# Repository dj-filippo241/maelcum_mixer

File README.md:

# Maelcum Mixer

A one-off, fully analogue, modular dub performance mixer for a 5-way sound system.

Musical decisions and panel layout: Filippo. Engineering (topologies, simulations, PCB generation): Claude, under Filippo's review.

**Status.** Nothing has been built or measured on a bench yet. Every circuit number comes from LTspice simulation or from Python models. The musical behaviour (control laws, saturators, filter character) is being validated by ear on a Max for Live prototype. Component purchases are on hold until that prototype is complete. The PCBs are generated drafts.

## Start here

- **Technical dossier (English):** [`docs/dossier-en/maelcum-mixer-dossier.pdf`](docs/dossier-en/maelcum-mixer-dossier.pdf), also as [HTML](docs/dossier-en/dossier.html). It is the complete English entry point: architecture, every module, numbers and their sources.
- **Block diagrams (English):** [`docs/diagrammi/en/`](docs/diagrammi/en/index.html), starting from [`schema-totale.svg`](docs/diagrammi/en/schema-totale.svg).

The rest of the repository is written in Italian. Technical terms stay in English where they are standard (headroom, summing, feedback, taper).

## Architecture in one paragraph

Four DJ channels (CDJ/line, optional MM phono) with a 4-band isolator EQ and a VCA fader. A shared global filter (HPF and LPF buses after the fader, Xone:96-style law, OTA core with overdrive). A 5-way performance EQ / dub preamp with a kill per band, matching the crossover of the sound system. Four FX buses with a 16-VCA feedback matrix. Mic and generic mono modules. Master, booth and record outputs, CUE, metering in six zones. Design targets: 0 dBu nominal, system headroom of at least +24 dBu (master clips at about +25.5 dBu), no automatic dynamics, nonlinearity only where intended. Simulated system noise: about -83 dBu A-weighted with filters off.

## Repository map

| Path | Content |
|---|---|
| `SPECIFICA.md` | Consolidated specification |
| `docs/01-decisioni-bloccate.md` | Locked decisions, with date and origin |
| `docs/02-questioni-aperte.md` | Open questions |
| `docs/fase1/` ... `docs/fase4/` | Design documents per module |
| `sim/` | LTspice netlists (`.cir`) and results (`RISULTATI-*.md`); shared models in `sim/lib/` |
| `pcb/` | KiCad schematics and 4-layer PCBs, generated by `pcb/<module>/<module>.py` with `pcb/tools/pcbgen.py` |
| `proto-max/` | Max for Live prototype: generators and tests in `proto-max/coefficienti/` |
| `docs/pannelli/` | Panel renders |
| `cheap/` | A parallel low-cost variant, on hold |

Status tags used in the documents: BLOCCATO (locked), PROVVISORIO (provisional), APERTO (open), SUPERATO (superseded, kept as an alternative or as evidence of a dead end).

## Tools

- LTspice 26.0.2, run in batch with `sim/run_ltspice.sh <netlist.cir>`.
- KiCad 10.0.7 with Freerouting; boards are regenerated from their Python script, never edited by hand.
- Max for Live (gen~) for the prototype; the `.genexpr`, `.maxpat` and `.amxd` files are generated.

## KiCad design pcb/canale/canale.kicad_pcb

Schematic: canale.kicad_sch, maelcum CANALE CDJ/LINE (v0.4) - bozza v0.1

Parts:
C1, C2: 220u 35V; CP_Radial_D8.0mm_P3.50mm
C3: 47u 10V; CP_Radial_D5.0mm_P2.00mm
C4, C8: 10u 35V; CP_Radial_D5.0mm_P2.00mm
C5, C9: 47u 35V; CP_Radial_D6.3mm_P2.50mm
C6, C10: 470u 25V; CP_Radial_D8.0mm_P3.50mm
C7, C11: 100u 25V; CP_Radial_D6.3mm_P2.50mm
C12, C13: 1u 50V; C_1206_3216Metric
C14, C15: 1u 25V; C_1206_3216Metric
C16, C17, C19, C20: 4u7 25V; C_1206_3216Metric
C18, C21: 10u 25V; C_1206_3216Metric
C22: 1u; C_1206_3216Metric
C23, C24, C27, C28, C29, C30, C58, C59, C60, C61, C62, C63, C64, C65, C66, C67, C96, C97, C98, C99, C100, C101, C102, C103, C104, C105, C107, C108, C109, C110, C111, C112, C113, C114, C117, C118, C119, C120, C122, C123, C125, C126, C127, C128, C131, C132, C133, C134, C135, C136, C137, C139, C140, C141, C142, C143: 100n; C_0805_2012Metric
C25, C26: 2u2 film; C_1812_4532Metric
C31, C32, C42, C43, C69, C70, C80, C81: 220n C0G; C_1210_3225Metric
C33, C34, C35, C36, C49, C51, C71, C72, C73, C74, C87, C89: 100n C0G; C_1210_3225Metric
C37, C38, C39, C40, C41, C57, C75, C76, C77, C78, C79, C95: 10n C0G; C_1206_3216Metric
C44, C82: 94n C0G; C_1210_3225Metric
C45, C83: 47n C0G; C_1210_3225Metric
C46, C52, C84, C90: 9n4 C0G; C_1206_3216Metric
C47, C53, C55, C85, C91, C93: 4n7 C0G; C_1206_3216Metric
C48, C50, C86, C88: 200n C0G; C_1210_3225Metric
C54, C92: 21n15 C0G; C_1206_3216Metric
C56, C94: 20n C0G; C_1206_3216Metric
C68, C106: 27n C0G; C_1206_3216Metric
C115: 47p C0G; C_0805_2012Metric
C116: 100n C0G; C_1206_3216Metric
C121, C124: 22p C0G; C_0805_2012Metric
C129, C130: 50n C0G; C_1206_3216Metric
C138: 47n; C_0805_2012Metric
D1, D3, D8, D9, D10, D11, D12, D13, D14: 1N4148W; D_SOD-123
D2, D4: S1G; D_SMA
D5: LM4040-5.0; SOT-23
D6, D7: TVS bidir <=5 pF; D_SOD-323
FB1, FB2, FB3, FB4, FB5, FB6, FB7: ferrite 600R; L_1206_3216Metric
H1, H2, H3: CHASSIS; MountingHole_3.2mm_M3_Pad
J1: C96 maschio; DIN41612_C_3x32_Male_Horizontal_THT
J2: 2x18 cavo piatto; PinHeader_2x18_P2.54mm_Vertical
J3: 1x5 ingressi; PinHeader_1x05_P2.54mm_Vertical
Q40: BD139; TO-126-3_Vertical
Q41: BD140; TO-126-3_Vertical
R1, R4: 120 1%; R_0805_2012Metric
R2, R5: 1k74 1%; R_0805_2012Metric
R3, R6, R127, R164, R165: 1k; R_0805_2012Metric
R7, R8: 150k 0.1%; R_0805_2012Metric
R9: 1k5; R_0805_2012Metric
R10, R11, R37, R39, R43, R45, R53, R55, R86, R88, R92, R94, R102, R104, R146, R168, R169, R170, R171, R172, R173: 10k 0.1%; R_0805_2012Metric
R12, R17: 100; R_0805_2012Metric
R13, R18, R69, R118, R149, R162, R167: 100k; R_0805_2012Metric
R14, R19: 4k30 0.1%; R_0805_2012Metric
R15, R20: 2k15 0.1%; R_0805_2012Metric
R16, R21, R151, R153: 1k 0.1%; R_0805_2012Metric
R22, R23, R32, R33, R71, R72, R81, R82: 4k81 0.1%; R_0805_2012Metric
R24, R26, R46, R47, R48, R49, R73, R75, R95, R96, R97, R98: 3k20 0.1%; R_0805_2012Metric
R25, R27, R74, R76: 6k42 0.1%; R_0805_2012Metric
R28, R77: 2k37 0.1%; R_0805_2012Metric
R29, R78: 10k7 0.1%; R_0805_2012Metric
R30, R59, R60, R79, R108, R109: 3k57 0.1%; R_0805_2012Metric
R31, R80: 7k15 0.1%; R_0805_2012Metric
R34, R83: 6k81 0.1%; R_0805_2012Metric
R35, R84: 13k7 0.1%; R_0805_2012Metric
R36, R85: 10k2 0.1%; R_0805_2012Metric
R38, R44, R54, R87, R93, R103, R157: 4k99 0.1%; R_0805_2012Metric
R40, R50, R89, R99: 7k59 0.1%; R_0805_2012Metric
R41, R51, R90, R100: 15k2 0.1%; R_0805_2012Metric
R42, R52, R91, R101: 11k4 0.1%; R_0805_2012Metric
R56, R57, R58, R105, R106, R107: 5k05 0.1%; R_0805_2012Metric
R61, R62, R63, R64, R110, R111, R112, R113: 2k49 0.1%; R_0805_2012Metric
R65, R114: 2k 0.1%; R_0805_2012Metric
R66, R115: 1k8 0.1%; R_0805_2012Metric
R67, R116: 200 0.1%; R_0805_2012Metric
R68, R117: 1M; R_0805_2012Metric
R70, R119: 499 0.1%; R_0805_2012Metric
R120, R121, R122, R123: 47; R_0805_2012Metric
R124, R125, R129, R133, R134, R138: 20k 0.1%; R_0805_2012Metric
R126: 4k02 0.1%; R_0805_2012Metric
R128: 3M; R_0805_2012Metric
R130, R135: 6k19; R_0805_2012Metric
R131, R136: 150k; R_0805_2012Metric
R132, R137: 51; R_0805_2012Metric
R139: 43.2k 0.1%; R_0805_2012Metric
R140: 68.1k 0.1%; R_0805_2012Metric
R141: 357k 0.1%; R_0805_2012Metric
R142: 20.0k 0.1%; R_0805_2012Metric
R143: 38.3k 0.1%; R_0805_2012Metric
R144: 976 0.1%; R_0805_2012Metric
R145: 1.33k 0.1%; R_0805_2012Metric
R147: 9k76 0.1%; R_0805_2012Metric
R148: 18k7 0.1%; R_0805_2012Metric
R150: 18k2 0.1%; R_0805_2012Metric
R152: 17k4 0.1%; R_0805_2012Metric
R154: 2M7; R_0805_2012Metric
R155, R156, R158, R159, R160, R161, R166: 10k; R_0805_2012Metric
R163: 68k; R_0805_2012Metric
RV1, RV2, RV4: 50k; Potentiometer_Bourns_3266W_Vertical
RV3: 2k; Potentiometer_Bourns_3266W_Vertical
U1, U2, U13, U15, U16, U20, U21, U22, U46: OPA1612AIDR; SOIC-8_3.9x4.9mm_P1.27mm
U3, U4, U5, U6, U7, U8, U9, U10, U11, U12, U17: OPA1654AIDR; SOIC-14_3.9x8.7mm_P1.27mm
U14: OPA1642AIDR; SOIC-8_3.9x4.9mm_P1.27mm
U18, U19: V2181L; SOIC-8_3.9x4.9mm_P1.27mm
U23: 74HC14PW; TSSOP-14_4.4x5mm_P0.65mm
U24: 74HC86PW; TSSOP-14_4.4x5mm_P0.65mm
U25: 74HC74PW; TSSOP-14_4.4x5mm_P0.65mm
U26, U27: ADG1434YRUZ; TSSOP-20_4.4x6.5mm_P0.65mm
U40: LM317; TO-220-3_Vertical
U41: LM337; TO-220-3_Vertical
U42: 78L15; SOT-89-3
U43: 79L15; SOT-89-3
U44: LT3045EMSE; MSOP-12-1EP_3x4.039mm_P0.65mm_EP1.651x2.845mm
U45: LT3094EMSE; MSOP-12-1EP_3x4.039mm_P0.65mm_EP1.651x2.845mm

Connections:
+5V: FB5.1, J1.a21, J1.a22
+5VF: C3.1, C135.1, C136.1, C137.1, FB5.2, J2.33, R158.1, R160.1, U23.14 (VCC), U24.13 (4B), U24.14 (VCC), U25.1 (1CLR), U25.4 (1PRE), U25.10 (2PRE), U25.13 (2CLR), U25.14 (VCC)
+15LN: C18.1, C23.1, C127.1, C131.1, R9.1, RV1.1, RV2.1, RV4.1, U21.8 (V+), U22.8 (V+), U44.10 (OUTS), U44.11 (OUT), U44.12 (OUT), U46.8 (V+)
+15SW: C14.1, C140.1, C142.1, U26.16 (VDD), U27.16 (VDD), U42.1 (OUT)
+18V: C7.1, C17.1, C27.1, C29.1, C58.1, C60.1, C62.1, C64.1, C66.1, C96.1, C98.1, C100.1, C102.1, C104.1, C107.1, C109.1, C111.1, C113.1, C117.1, C119.1, C122.1, C125.1, Q40.1 (E), U1.8 (V+), U2.8 (V+), U3.4 (V+), U4.4 (V+), U5.4 (V+), U6.4 (V+), U7.4 (V+), U8.4 (V+), U9.4 (V+), U10.4 (V+), U11.4 (V+), U12.4 (V+), U13.8 (V+), U14.8 (V+), U15.8 (V+), U16.8 (V+), U17.4 (V+), U18.7 (V+), U19.7 (V+), U20.8 (V+), U44.1 (IN), U44.2 (IN), U44.3 (IN), U44.4 (EN/UV), U44.7 (PGFB)
+REF5: J2.26, R10.1, U46.1, U46.2 (-)
-15LN: C21.2, C24.2, C128.2, C132.2, RV1.3, RV2.3, RV4.3, U21.4 (V-), U22.4 (V-), U45.10 (OUTS), U45.11 (OUT), U45.12 (OUT), U46.4 (V-)
-15SW: C15.2, C141.2, C143.2, U26.5 (VSS), U27.5 (VSS), U43.3 (VO)
-18V: C11.2, C20.2, C28.2, C30.2, C59.2, C61.2, C63.2, C65.2, C67.2, C97.2, C99.2, C101.2, C103.2, C105.2, C108.2, C110.2, C112.2, C114.2, C118.2, C120.2, C123.2, C126.2, Q41.1 (E), R130.2, R135.2, U1.4 (V-), U2.4 (V-), U3.11 (V-), U4.11 (V-), U5.11 (V-), U6.11 (V-), U7.11 (V-), U8.11 (V-), U9.11 (V-), U10.11 (V-), U11.11 (V-), U12.11 (V-), U13.4 (V-), U14.4 (V-), U15.4 (V-), U16.4 (V-), U17.11 (V-), U20.4 (V-), U45.1 (IN), U45.2 (IN), U45.3 (EN/UV), U45.5 (PGFB), U45.13 (IN)
-REF5: R11.2, R141.2, R143.2, R145.2, U46.7
ADJ+: C4.1, D1.2 (A), R1.2, R2.1, U40.1 (ADJ)
ADJ-: C8.2, D3.1 (K), R4.2, R5.1, U41.1 (ADJ)
AGND: C1.2, C2.1, C4.2, C5.2, C6.2, C7.2, C8.1, C9.1, C10.1, C11.1, C12.2, C13.1, C14.2, C15.1, C16.2, C17.2, C18.2, C19.1, C20.1, C21.1, C22.2, C23.2, C24.1, C27.2, C28.1, C29.2, C30.1, C43.2, C49.2, C51.2, C54.2, C57.2, C58.2, C59.1, C60.2, C61.1, C62.2, C63.1, C64.2, C65.1, C66.2, C67.1, C81.2, C87.2, C89.2, C92.2, C95.2, C96.2, C97.1, C98.2, C99.1, C100.2, C101.1, C102.2, C103.1, C104.2, C105.1, C107.2, C108.1, C109.2, C110.1, C111.2, C112.1, C113.2, C114.1, C116.2, C117.2, C118.1, C119.2, C120.1, C122.2, C123.1, C125.2, C126.1, C127.2, C128.1, C129.2, C130.2, C131.2, C132.1, C140.2, C141.1, C142.2, C143.1, D5.2 (A), D6.2 (A2), D7.2 (A2), J1.a13, J1.a14, J1.a15, J1.a16, J1.a17, J1.a18, J1.a19, J1.a20, J1.b3, J1.b6, J1.b9, J1.b12, J1.b15, J1.b18, J1.b21, J1.b24, J1.b27, J1.b30, J2.1, J2.4, J2.7, J2.16, J2.25, J2.28, J2.35, J2.36, J3.2, J3.4, R2.2, R5.2, R7.2, R8.2, R13.2, R14.2, R16.2, R18.2, R19.2, R21.2, R23.2, R25.2, R27.2, R28.2, R31.2, R35.2, R41.2, R51.2, R67.2, R70.2, R72.2, R74.2, R76.2, R77.2, R80.2, R84.2, R90.2, R100.2, R116.2, R119.2, R126.2, R128.2, R132.2, R137.2, R149.2, R151.2, R153.2, U3.12 (+), U4.10 (+), U4.12 (+), U5.3 (+), U5.5 (+), U6.3 (+), U6.5 (+), U6.10 (+), U8.12 (+), U9.10 (+), U9.12 (+), U10.3 (+), U10.5 (+), U11.3 (+), U11.5 (+), U11.10 (+), U14.3 (+), U14.5 (+), U17.12 (+), U18.2 (EC+), U18.6 (GND), U19.2 (EC+), U19.6 (GND), U20.3 (+), U20.5 (+), U21.3 (+), U21.5 (+), U26.4 (S1B), U26.6 (GND), U26.7 (S2B), U26.14 (S3B), U26.17 (S4B), U27.4 (S1B), U27.6 (GND), U27.7 (S2B), U27.14 (S3B), U27.17 (S4B), U42.2 (GND), U43.1 (GND), U44.6 (ILIM), U44.9 (GND), U44.13 (GND), U45.6 (ILIM), U45.9 (GND), U46.5 (+)
APBP1_L: C45.2, R36.2, R38.1, U4.8
APBP1_R: C83.2, R85.2, R87.1, U9.8
APBP2_L: C47.2, R42.2, R44.1, U5.1
APBP2_R: C85.2, R91.2, R93.1, U10.1
APBP3_L: C53.2, R52.2, R54.1, U6.1
APBP3_R: C91.2, R101.2, R103.1, U11.1
APMP1_L: C44.2, R36.1, U4.9 (-)
APMP1_R: C82.2, R85.1, U9.9 (-)
APMP2_L: C46.2, R42.1, U5.2 (-)
APMP2_R: C84.2, R91.1, U10.2 (-)
APMP3_L: C52.2, R52.1, U6.2 (-)
APMP3_R: C90.2, R101.1, U11.2 (-)
APNP1_L: C44.1, C45.1, R34.2, R35.1
APNP1_R: C82.1, C83.1, R83.2, R84.1
APNP2_L: C46.1, C47.1, R40.2, R41.1
APNP2_R: C84.1, C85.1, R89.2, R90.1
APNP3_L: C52.1, C53.1, R50.2, R51.1
APNP3_R: C90.1, C91.1, R99.2, R100.1
APSP1_L: R37.2, R38.2, R39.1, U4.13 (-)
APSP1_R: R86.2, R87.2, R88.1, U9.13 (-)
APSP2_L: R43.2, R44.2, R45.1, U5.6 (-)
APSP2_R: R92.2, R93.2, R94.1, U10.6 (-)
APSP3_L: R53.2, R54.2, R55.1, U6.6 (-)
APSP3_R: R102.2, R103.2, R104.1, U11.6 (-)
BASE+: C6.1, Q40.3 (B), R3.2
BASE-: C10.2, Q41.3 (B), R6.2
BTNC: J2.32, R166.1
BUF_L: J2.2, U1.1, U1.2 (-)
BUF_R: J2.5, U1.6 (-), U1.7
BUS_HPF_L: J1.b10, R169.2
BUS_HPF_R: J1.b11, R172.2
BUS_LPF_L: J1.b13, R170.2
BUS_LPF_R: J1.b14, R173.2
CHASSIS: H1.1, H2.1, H3.1, J1.a25, J1.a26, J3.5
CLK: U23.8 (4Y), U25.3 (1CLK), U25.11 (2CLK)
CTRL_GND: C3.2, C133.2, C134.2, C135.2, C136.2, C137.2, C138.2, C139.2, J1.a23, J1.a24, J1.c16, J1.c20, J1.c24, J1.c28, J2.34, R162.2, R167.2, U23.7 (GND), U24.7 (GND), U25.7 (GND)
CUEB_L: U15.1, U15.2 (-), U26.19 (S4A)
CUEB_R: U16.1, U16.2 (-), U27.19 (S4A)
CUED_L: R121.1, U26.18 (D4)
CUED_R: R123.1, U27.18 (D4)
CUESEL: C139.1, R166.2, R167.1, U26.20 (IN4), U27.20 (IN4)
CUE_OUT_L: J1.b4, R121.2
CUE_OUT_R: J1.b5, R123.2
CVP_F: R148.2, R150.1, R152.1, U21.7
D0: U23.2 (1Y), U24.1 (1A), U25.2 (1D)
D1: U23.4 (2Y), U24.4 (2A), U25.12 (2D)
D1A: D8.2 (A), R127.2
DIFF: D12.1 (K), D13.1 (K), R162.1, U23.13 (6A)
DIFFB: D14.1 (K), R155.1, R163.1, U24.11 (4Y)
DIPCV: R157.1, U22.6 (-), U22.7
DJBUS_L: J1.b1, R168.2
DJBUS_R: J1.b2, R171.2
DJD_L: R168.1, U26.3 (D1)
DJD_R: R171.1, U27.3 (D1)
DJSEL: U23.10 (5Y), U26.1 (IN1), U27.1 (IN1)
DLY: C138.1, D14.2 (A), R163.2, U23.5 (3A)
DOUT: C115.1, R127.1, U17.7
DP1: C129.1, R155.2, U22.3 (+)
DP2: C130.1, R156.2, U22.5 (+)
DPB1: R156.1, U22.1, U22.2 (-)
ECF_L: R150.2, R151.1, U18.3 (EC-)
ECF_R: R153.1, R154.2, RV3.2, RV3.3, U19.3 (EC-)
EQ_L: R66.2, R68.1, R124.1, R129.1, U13.1, U15.3 (+), U15.5 (+)
EQ_R: R115.2, R117.1, R125.1, R134.1, U13.7, U16.3 (+), U16.5 (+)
FAD_L: C121.2, R133.2, U20.1, U26.2 (S1A), U26.9 (S2A), U26.12 (S3A)
FAD_R: C124.2, R138.2, U20.7, U27.2 (S1A), U27.9 (S2A), U27.12 (S3A)
FILT_MODE1_0: J1.c1, R164.2
FILT_MODE1_1: J1.c2, R165.2
FR0: C133.1, R159.2, U23.1 (1A)
FR1: C134.1, R161.2, U23.3 (2A)
FSW0: J2.30, R158.2, R159.1
FSW1: J2.31, R160.2, R161.1
GO_L: C31.1, R15.1, R32.1, U2.1
GO_R: C69.1, R20.1, R81.1, U2.7
GW_L: J2.3, R14.1, U2.3 (+)
GW_R: J2.6, R19.1, U2.5 (+)
HA_L: C55.2, R57.2, R59.1, U6.8
HA_R: C93.2, R106.2, R108.1, U11.8
HIO_L: J2.14, R30.2, U4.1, U4.2 (-)
HIO_R: J2.23, R79.2, U9.1, U9.2 (-)
HOLD: C115.2, C116.1, D8.1 (K), R128.1, U17.6 (-), U17.10 (+)
HPD_L: R169.1, U26.8 (D2)
HPD_R: R172.1, U27.8 (D2)
INC_L: C25.2, R13.1, U1.3 (+)
INC_R: C26.2, R18.1, U1.5 (+)
INF_L: FB6.2, R12.1
INF_R: FB7.2, R17.1
INP_L: C25.1, D6.1 (A1), R12.2
INP_R: C26.1, D7.1 (A1), R17.2
IN_L: FB6.1, J3.1
IN_R: FB7.1, J3.3
K1W_L: J2.9, U7.3 (+)
K1W_R: J2.18, U12.3 (+)
K1_L: R61.1, U7.1, U7.2 (-)
K1_R: R110.1, U12.1, U12.2 (-)
K2W_L: J2.11, U7.5 (+)
K2W_R: J2.20, U12.5 (+)
K2_L: R62.1, U7.6 (-), U7.7
K2_R: R111.1, U12.6 (-), U12.7
K3W_L: J2.13, U7.10 (+)
K3W_R: J2.22, U12.10 (+)
K3_L: R63.1, U7.8, U7.9 (-)
K3_R: R112.1, U12.8, U12.9 (-)
K4W_L: J2.15, U7.12 (+)
K4W_R: J2.24, U12.12 (+)
K4_L: R64.1, U7.13 (-), U7.14
K4_R: R113.1, U12.13 (-), U12.14
LA_L: C42.2, R34.1, R37.1, U4.6 (-), U4.7
LA_R: C80.2, R83.1, R86.1, U9.6 (-), U9.7
LB_L: R39.2, R40.1, R43.1, U4.14
LB_R: R88.2, R89.1, R92.1, U9.14
LMO_L: J2.10, R55.2, U6.7
LMO_R: J2.19, R104.2, U11.7
LOO_L: J2.8, R45.2, U5.7
LOO_R: J2.17, R94.2, U10.7
LPD_L: R170.1, U26.13 (D3)
LPD_R: R173.1, U27.13 (D3)
LT_F: R152.2, RV3.1
MA_L: C48.2, R48.1, U5.8, U5.9 (-)
MA_R: C86.2, R97.1, U10.8, U10.9 (-)
MB_L: C50.2, R50.1, R53.1, U5.13 (-), U5.14
MB_R: C88.2, R99.1, R102.1, U10.13 (-), U10.14
MCN_L: C55.1, R58.2, U6.9 (-)
MCN_R: C93.1, R107.2, U11.9 (-)
MCX_L: C54.1, R56.2, R57.1, R58.1
MCX_R: C92.1, R105.2, R106.1, R107.1
MET: J2.29, U17.8, U17.9 (-)
MG: R124.2, R125.2, R126.1, U17.3 (+)
MGB: U17.1, U17.2 (-), U17.5 (+)
MHN_L: C39.2, R29.1, U3.13 (-)
MHN_R: C77.2, R78.1, U8.13 (-)
MHO_L: C56.2, J2.12, U6.13 (-), U6.14
MHO_R: C94.2, J2.21, U11.13 (-), U11.14
MHX_L: C37.2, C38.1, C39.1, R28.1
MHX_R: C75.2, C76.1, C77.1, R77.1
NCLK: U23.6 (3Y), U23.9 (4A)
NDIFF: U23.12 (6Y), U24.12 (4A)
NGS_L: R66.1, R67.1, U13.2 (-)
NGS_R: R115.1, R116.1, U13.6 (-)
NG_L: R15.2, R16.1, U2.2 (-)
NG_R: R20.2, R21.1, U2.6 (-)
NIF_L: C121.1, R133.1, U18.8 (OUT), U20.2 (-)
NIF_R: C124.1, R138.1, U19.8 (OUT), U20.6 (-)
NP_F: R147.2, R148.1, U21.6 (-)
NREF5I: R10.2, R11.1, U46.6 (-)
NU17: U17.13 (-), U17.14
OF_F: R154.1, RV4.2
POT_F: J2.27, R139.1, R140.1, R142.1, R144.1, R149.1
Q0: R164.1, U24.2 (1B), U24.9 (3A), U25.5 (1Q), U26.10 (IN2), U27.10 (IN2)
Q1: R165.1, U24.5 (2B), U24.10 (3B), U25.9 (2Q), U26.11 (IN3), U27.11 (IN3)
R1_L: C33.1, R22.2, R46.1, U3.1, U3.2 (-)
R1_R: C71.1, R71.2, R95.1, U8.1, U8.2 (-)
R2A_L: C35.1, R24.2, U3.6 (-), U3.7
R2A_R: C73.1, R73.2, U8.6 (-), U8.7
R2_L: C37.1, R26.2, R56.1, U3.8, U3.9 (-)
R2_R: C75.1, R75.2, R105.1, U8.8, U8.9 (-)
R3A_L: C38.2, C40.1, R29.2, U3.14
R3A_R: C76.2, C78.1, R78.2, U8.14
RAW+22: FB3.1, J1.a5, J1.a6
RAW+27: FB1.1, J1.a1, J1.a2
RAW-22: FB4.1, J1.a7, J1.a8
RAW-27: FB2.1, J1.a3, J1.a4
REF5K: C22.1, D5.1 (K), R9.2, U46.3 (+)
SEND_TAP_L: J1.b7, R120.2
SEND_TAP_R: J1.b8, R122.2
SETN: C19.2, R8.1, U45.8 (SET)
SETP: C16.1, R7.1, U44.8 (SET)
SH_F: R146.2, R147.1, U21.1
SJ_F: D9.1 (K), D10.1 (K), D11.1 (K), R139.2, R146.1, R157.2, U21.2 (-)
SKAA1_L: C42.1, R32.2, R33.1
SKAA1_R: C80.1, R81.2, R82.1
SKAB1_L: C48.1, R46.2, R47.1
SKAB1_R: C86.1, R95.2, R96.1
SKAB2_L: C50.1, R48.2, R49.1
SKAB2_R: C88.1, R97.2, R98.1
SKAC2_L: C56.1, R59.2, R60.1
SKAC2_R: C94.1, R108.2, R109.1
SKAG2_L: C35.2, C36.1, R26.1
SKAG2_R: C73.2, C74.1, R75.1
SKAH1_L: C31.2, C32.1, R22.1
SKAH1_R: C69.2, C70.1, R71.1
SKAH2_L: C33.2, C34.1, R24.1
SKAH2_R: C71.2, C72.1, R73.1
SKAH3B_L: C40.2, C41.1, R30.1
SKAH3B_R: C78.2, C79.1, R79.1
SKBA1_L: C43.1, R33.2, U4.5 (+)
SKBA1_R: C81.1, R82.2, U9.5 (+)
SKBB1_L: C49.1, R47.2, U5.10 (+)
SKBB1_R: C87.1, R96.2, U10.10 (+)
SKBB2_L: C51.1, R49.2, U5.12 (+)
SKBB2_R: C89.1, R98.2, U10.12 (+)
SKBC2_L: C57.1, R60.2, U6.12 (+)
SKBC2_R: C95.1, R109.2, U11.12 (+)
SKBG2_L: C36.2, R27.1, U3.10 (+)
SKBG2_R: C74.2, R76.1, U8.10 (+)
SKBH1_L: C32.2, R23.1, U3.3 (+)
SKBH1_R: C70.2, R72.1, U8.3 (+)
SKBH2_L: C34.2, R25.1, U3.5 (+)
SKBH2_R: C72.2, R74.1, U8.5 (+)
SKBH3B_L: C41.2, R31.1, U4.3 (+)
SKBH3B_R: C79.2, R80.1, U9.3 (+)
SN1_F: D9.2 (A), R140.2, R141.1
SN2_F: D10.2 (A), R142.2, R143.1
SN3_F: D11.2 (A), R144.2, R145.1
SP_L: R61.2, R62.2, R63.2, R64.2, R65.2, U13.3 (+)
SP_R: R110.2, R111.2, R112.2, R113.2, R114.2, U13.5 (+)
STB_L: R120.1, U15.6 (-), U15.7
STB_R: R122.1, U16.6 (-), U16.7
SVI_L: C68.1, R68.2, U14.2 (-)
SVI_R: C106.1, R117.2, U14.6 (-)
SVO_L: C68.2, R69.1, U14.1
SVO_R: C106.2, R118.1, U14.7
SV_L: R65.1, R69.2, R70.1
SV_R: R114.1, R118.2, R119.1
SW_fl: R131.1, RV1.2
SW_fr: R136.1, RV2.2
SYM_fl: R131.2, R132.1, U18.4 (SYM)
SYM_fr: R136.2, R137.1, U19.4 (SYM)
V22F+: C12.1, FB3.2, U42.3 (IN)
V22F-: C13.2, FB4.2, U43.2 (VI)
V27F+: C1.1, D2.1 (K), FB1.2, U40.3 (VI)
V27F-: C2.2, D4.2 (A), FB2.2, U41.2 (VI)
VEE_fl: R130.1, U18.5 (V-)
VEE_fr: R135.1, U19.5 (V-)
VIN_fl: R129.2, U18.1 (IN)
VIN_fr: R134.2, U19.1 (IN)
VREG+: C5.1, D1.1 (K), D2.2 (A), Q40.2 (C), R1.1, R3.1, U40.2 (VO)
VREG-: C9.2, D3.2 (A), D4.1 (K), Q41.2 (C), R4.1, R6.1, U41.3 (VO)
X0: D12.2 (A), U24.3 (1Y)
X1: D13.2 (A), U24.6 (2Y)
XQ: U23.11 (5A), U24.8 (3Y)

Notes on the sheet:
BACKPLANE C96 (classe CDJ, REV dec. 159)
ALIMENTAZIONE +-18 audio, +-15 switch, +5, +-15 LN, +-5 riferimento
INGRESSO LINE [A] e GAIN T1 [B] (dec. 162)
ISOLATOR lato L (incroci C, dec. 152; iso-incc-banca.inc)
ISOLATOR lato R (incroci C, dec. 152; iso-incc-banca.inc)
SOMMA DELL'ISOLATOR (non invertente) e SERVO DC
CUE [D], SEND TAP [E] e METER [G] (pre-fader)
FADER [H] (2 VCA, shaper del fader, dec. 126) e DIP (dec. 163)
LEVETTA HPF/OFF/LPF: logica autotemporizzata (74HC14, 74HC86, 74HC74) e ADG1434
CAVO SCHEDA COMANDI (J2) e INGRESSI RCA (J3)

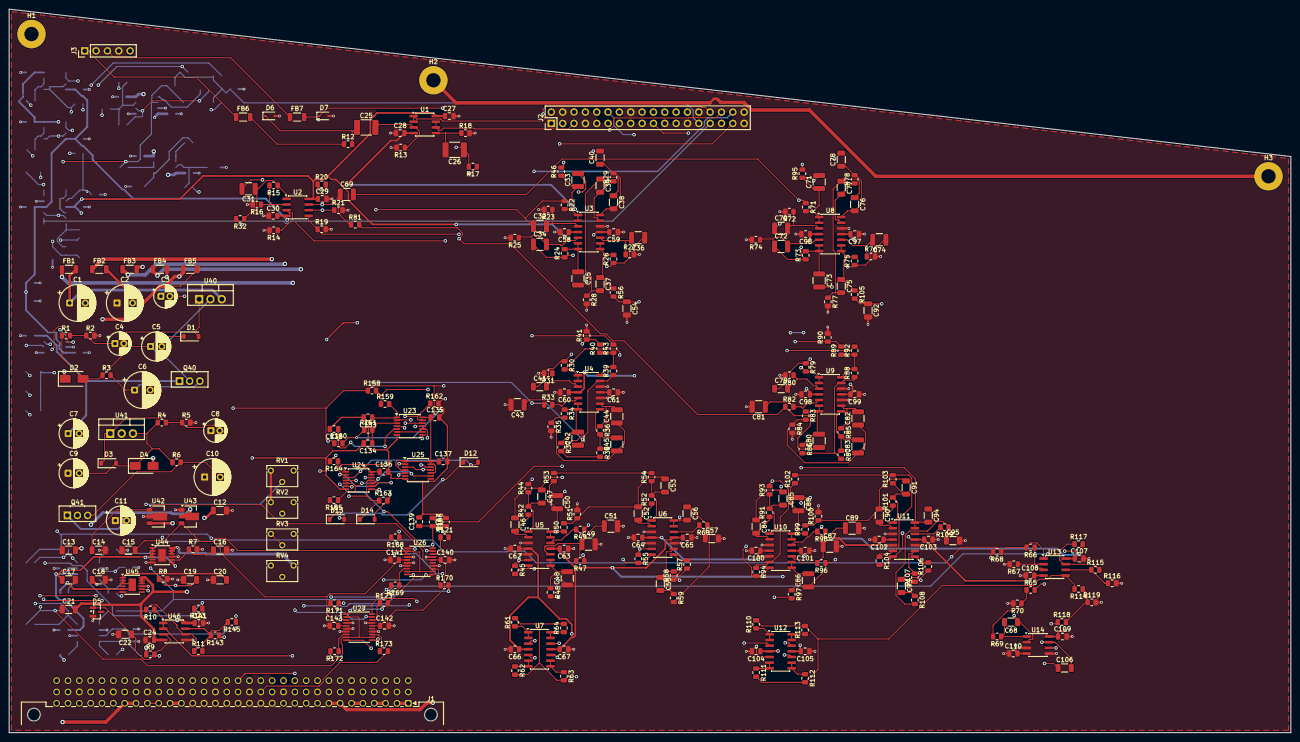
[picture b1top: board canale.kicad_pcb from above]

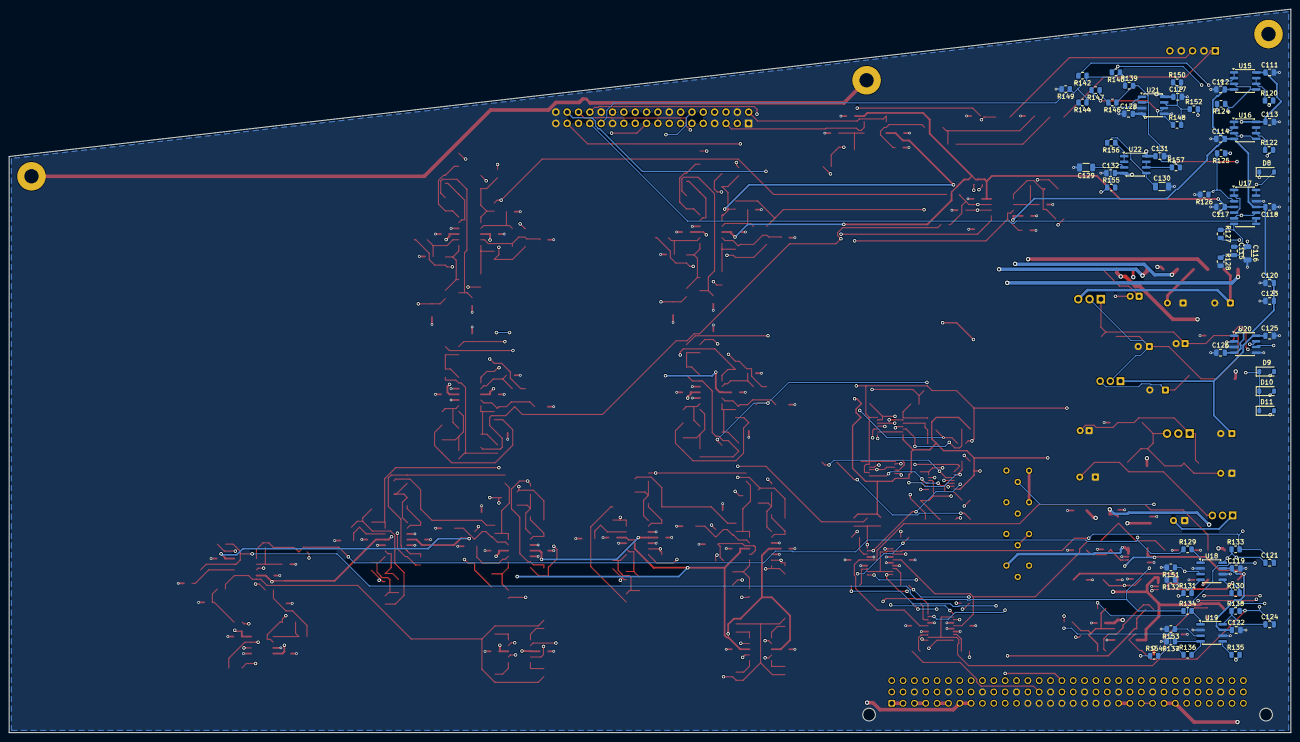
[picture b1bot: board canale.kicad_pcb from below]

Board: 4 copper layers, 287.0 x 162.0 mm, 383 parts (67 on the bottom side), 244 nets.

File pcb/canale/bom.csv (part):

quantita;valore;impronta;riferimenti;nota
2;220u 35V;CP_Radial_D8.0mm_P3.50mm;C1 C2;
1;47p C0G;C_0805_2012Metric;C115;
1;100n C0G;C_1206_3216Metric;C116;hold: niente altro sul nodo (sim/meter)
2;1u 50V;C_1206_3216Metric;C12 C13;
2;22p C0G;C_0805_2012Metric;C121 C124;
1;50n C0G;C_1206_3216Metric;C129;NOTA: 50n = 47n + 3n3 in parallelo; tau 0,5 ms
1;50n C0G;C_1206_3216Metric;C130;NOTA: 50n = 47n + 3n3 in parallelo
1;47n;C_0805_2012Metric;C138;
2;1u 25V;C_1206_3216Metric;C14 C15;
1;4u7 25V;C_1206_3216Metric;C16;rumore del riferimento (datasheet: 4,7 uF)
3;4u7 25V;C_1206_3216Metric;C17 C19 C20;
2;10u 25V;C_1206_3216Metric;C18 C21;
1;1u;C_1206_3216Metric;C22;
56;100n;C_0805_2012Metric;C23 C24 C27 C28 C29 C30 C58 C59 C60 C61 C62 C63 C64 C65 C66 C67 C96 C97 C98 C99 C100 C101 C102 C103 C104 C105 C107 C108 C109 C110 C111 C112 C113 C114 C117 C118 C119 C120 C122 C123 C125 C126 C127 C128 C131 C132 C133 C134 C135 C136 C137 C139 C140 C141 C142 C143;
2;2u2 film;C_1812_4532Metric;C25 C26;blocco della continua (voce 58)
1;47u 10V;CP_Radial_D5.0mm_P2.00mm;C3;
8;220n C0G;C_1210_3225Metric;C31 C32 C42 C43 C69 C70 C80 C81;
12;100n C0G;C_1210_3225Metric;C33 C34 C35 C36 C49 C51 C71 C72 C73 C74 C87 C89;
12;10n C0G;C_1206_3216Metric;C37 C38 C39 C40 C41 C57 C75 C76 C77 C78 C79 C95;
2;10u 35V;CP_Radial_D5.0mm_P2.00mm;C4 C8;
2;94n C0G;C_1210_3225Metric;C44 C82;NOTA: 2C, coppia in parallelo da fissare col layout (RISULTATI-incroci-C §1)
2;47n C0G;C_1210_3225Metric;C45 C83;
4;9n4 C0G;C_1206_3216Metric;C46 C52 C84 C90;NOTA: 2C, coppia in parallelo da fissare col layout (RISULTATI-incroci-C §1)
6;4n7 C0G;C_1206_3216Metric;C47 C53 C55 C85 C91 C93;
4;200n C0G;C_1210_3225Metric;C48 C50 C86 C88;NOTA: coppia in parallelo da fissare col layout
2;47u 35V;CP_Radial_D6.3mm_P2.50mm;C5 C9;
2;21n15 C0G;C_1206_3216Metric;C54 C92;NOTA: 4,5 x 4,7n, coppia in parallelo da fissare col layout
2;20n C0G;C_1206_3216Metric;C56 C94;NOTA: coppia in parallelo da fissare col layout
2;470u 25V;CP_Radial_D8.0mm_P3.50mm;C6 C10;
2;27n C0G;C_1206_3216Metric;C68 C106;integratore 1M/27n
2;100u 25V;CP_Radial_D6.3mm_P2.50mm;C7 C11;
1;1N4148W;D_SOD-123;D1;scarica Cadj
1;1N4148W;D_SOD-123;D12;NOTA: OR a diodi
1;1N4148W;D_SOD-123;D14;scarica il ritardo al rilascio: CLK giù in pochi us (todo 289)
1;S1G;D_SMA;D2;protezione inversa
6;1N4148W;D_SOD-123;D3 D8 D9 D10 D11 D13;
1;S1G;D_SMA;D4;
1;LM4040-5.0;SOT-23;D5;
2;TVS bidir <=5 pF;D_SOD-323;D6 D7;NOTA: parte da scegliere (TVS low-cap)
7;ferrite 600R;L_1206_3216Metric;FB1 FB2 FB3 FB4 FB5 FB6 FB7;
1;C96 maschio;DIN41612_C_3x32_Male_Horizontal_THT;J1;DIN 41612 C 3x32, angolo retto
1;2x18 cavo piatto;PinHeader_2x18_P2.54mm_Vertical;J2;cavo piatto corto verso la scheda comandi dietro il pannello (dec. 133)
1;1x5 ingressi;PinHeader_1x05_P2.54mm_Vertical;J3;NOTA: cavo verso gli RCA sulla schedina dei connettori (dec. 141)
1;BD139;TO-126-3_Vertical;Q40;
1;BD140;TO-126-3_Vertical;Q41;
2;120 1%;R_0805_2012Metric;R1 R4;
15;10k 0.1%;R_0805_2012Metric;R10 R11 R37 R39 R43 R45 R53 R55 R86 R88 R92 R94 R102 R104 R146;
2;100;R_0805_2012Metric;R12 R17;R serie (cdj §3.1)
2;47;R_0805_2012Metric;R120 R122;driver <= 50 ohm verso il FX-SEND (slot 3)
2;47;R_0805_2012Metric;R121 R123;NOTA: 47R dopo lo switch CUE (slot 2)
1;20k 0.1%;R_0805_2012Metric;R124;NOTA: barra unica del canale, (L+R)/2 con due 20k
5;20k 0.1%;R_0805_2012Metric;R125 R129 R133 R134 R138;
1;4k02 0.1%;R_0805_2012Metric;R126;g = 0,287 (doc 0,288), come il master
1;3M;R_0805_2012Metric;R128;release 0,3 s (dec. 81)
2;100k;R_0805_2012Metric;R13 R18;polo 0,72 Hz, Zin 100k
2;6k19;R_0805_2012Metric;R130 R135;5,1k del datasheet a -15 V riscalato a -18 V (come il master)
2;150k;R_0805_2012Metric;R131 R136;
2;51;R_0805_2012Metric;R132 R137;
1;43.2k 0.1%;R_0805_2012Metric;R139;
2;4k30 0.1%;R_0805_2012Metric;R14 R19;Rl dal cursore a massa (T1)
1;68.1k 0.1%;R_0805_2012Metric;R140;
1;357k 0.1%;R_0805_2012Metric;R141;
1;20.0k 0.1%;R_0805_2012Metric;R142;
1;38.3k 0.1%;R_0805_2012Metric;R143;
1;976 0.1%;R_0805_2012Metric;R144;
1;1.33k 0.1%;R_0805_2012Metric;R145;
1;9k76 0.1%;R_0805_2012Metric;R147;
1;18k7 0.1%;R_0805_2012Metric;R148;stadio del partitore x(-1,916): CV al pin = out/10,02 (todo 281)
1;100k;R_0805_2012Metric;R149;pot staccato = shaper a 0 V (come il master)
2;2k15 0.1%;R_0805_2012Metric;R15 R20;
1;18k2 0.1%;R_0805_2012Metric;R150;
2;1k 0.1%;R_0805_2012Metric;R151 R153;
1;17k4 0.1%;R_0805_2012Metric;R152;
1;2M7;R_0805_2012Metric;R154;partitore da ~950 ohm: 2,7M = +-5,3 mV come prima
2;10k;R_0805_2012Metric;R155 R156;
1;4k99 0.1%;R_0805_2012Metric;R157;NOTA: 4,4 V -> shaper -8,8 V -> stadio al rail -> 0,70-0,80 V al pin
2;10k;R_0805_2012Metric;R158 R160;levetta verso CTRL_GND sulla scheda comandi
2;10k;R_0805_2012Metric;R159 R161;NOTA: antirimbalzo 1 ms
2;1k 0.1%;R_0805_2012Metric;R16 R21;x3,15
1;68k;R_0805_2012Metric;R163;NOTA: 68k x 47n, ADG a 1,5-4 ms con le soglie del 74HC14 (todo 289)
1;1k;R_0805_2012Metric;R164;NOTA: bit di modo sulla riga c; il backplane li porta per posizione
1;10k;R_0805_2012Metric;R166;NOTA: tasto CUE a ritenuta verso +5VF
2;10k 0.1%;R_0805_2012Metric;R168 R171;R lato sorgente sul DJ bus
2;10k 0.1%;R_0805_2012Metric;R169 R172;R lato sorgente sul bus HPF
2;10k 0.1%;R_0805_2012Metric;R170 R173;R lato sorgente sul bus LPF
1;1k74 1%;R_0805_2012Metric;R2;E96 1,74k = 19,4 V (fx-send NOTE punto 16)
8;4k81 0.1%;R_0805_2012Metric;R22 R23 R32 R33 R71 R72 R81 R82;
12;3k20 0.1%;R_0805_2012Metric;R24 R26 R46 R47 R48 R49 R73 R75 R95 R96 R97 R98;
4;6k42 0.1%;R_0805_2012Metric;R25 R27 R74 R76;
2;2k37 0.1%;R_0805_2012Metric;R28 R77;calcolo 2,38k
2;10k7 0.1%;R_0805_2012Metric;R29 R78;
1;1k;R_0805_2012Metric;R3;NOTA: cap-moltiplicatore come il FX-SEND (~50 mA)
6;3k57 0.1%;R_0805_2012Metric;R30 R59 R60 R79 R108 R109;
2;7k15 0.1%;R_0805_2012Metric;R31 R80;
2;6k81 0.1%;R_0805_2012Metric;R34 R83;
2;13k7 0.1%;R_0805_2012Metric;R35 R84;
2;10k2 0.1%;R_0805_2012Metric;R36 R85;
6;4k99 0.1%;R_0805_2012Metric;R38 R44 R54 R87 R93 R103;sim 5k: E96 4,99k
4;7k59 0.1%;R_0805_2012Metric;R40 R50 R89 R99;
4;15k2 0.1%;R_0805_2012Metric;R41 R51 R90 R100;
4;11k4 0.1%;R_0805_2012Metric;R42 R52 R91 R101;
1;1k74 1%;R_0805_2012Metric;R5;
2;5k05 0.1%;R_0805_2012Metric;R56 R105;calcolo 5,07k
4;5k05 0.1%;R_0805_2012Metric;R57 R58 R106 R107;
3;1k;R_0805_2012Metric;R6 R127 R165;
8;2k49 0.1%;R_0805_2012Metric;R61 R62 R63 R64 R110 R111 R112 R113;
2;2k 0.1%;R_0805_2012Metric;R65 R114;ramo del servo
2;1k8 0.1%;R_0805_2012Metric;R66 R115;
2;200 0.1%;R_0805_2012Metric;R67 R116;
2;1M;R_0805_2012Metric;R68 R117;
4;100k;R_0805_2012Metric;R69 R118 R162 R167;
2;150k 0.1%;R_0805_2012Metric;R7 R8;
2;499 0.1%;R_0805_2012Metric;R70 R119;polo 0,058 Hz, corsa +-129 mV
1;1k5;R_0805_2012Metric;R9;NOTA: ~6,7 mA nel riferimento (come il master)
2;50k;Potentiometer_Bourns_3266W_Vertical;RV1 RV2;trim di simmetria (THD minima)
1;2k;Potentiometer_Bourns_3266W_Vertical;RV3;trim di law, 25 giri (vca-trim §3.2): montato solo se la coppia esce da 0,5 dB
1;50k;Potentiometer_Bourns_3266W_Vertical;RV4;trim d'offset di coppia
1;OPA1612AIDR;SOIC-8_3.9x4.9mm_P1.27mm;U1;buffer d'ingresso
1;OPA1654AIDR;SOIC-14_3.9x8.7mm_P1.27mm;U10;isolator lato R, sezioni 9-12
1;OPA1654AIDR;SOIC-14_3.9x8.7mm_P1.27mm;U11;isolator lato R, sezioni 13-16
1;OPA1654AIDR;SOIC-14_3.9x8.7mm_P1.27mm;U12;isolator lato R, sezioni 17-20
1;OPA1612AIDR;SOIC-8_3.9x4.9mm_P1.27mm;U13;somma x10 (2 per banda)
1;OPA1642AIDR;SOIC-8_3.9x4.9mm_P1.27mm;U14;servo DC (classe OPA2134 nel doc; OPA1642, SBOS484D)
1;OPA1612AIDR;SOIC-8_3.9x4.9mm_P1.27mm;U15;buffer CUE e SEND TAP, L
1;OPA1612AIDR;SOIC-8_3.9x4.9mm_P1.27mm;U16;buffer CUE e SEND TAP, R
1;OPA1654AIDR;SOIC-14_3.9x8.7mm_P1.27mm;U17;inseguitore di scala, superdiodo, buffer dell'hold (LM3915 sulla scheda comandi)
2;V2181L;SOIC-8_3.9x4.9mm_P1.27mm;U18 U19;
1;OPA1612AIDR;SOIC-8_3.9x4.9mm_P1.27mm;U2;GAIN T1, non invertente x3,15
1;OPA1612AIDR;SOIC-8_3.9x4.9mm_P1.27mm;U20;I/V del fader, pilota i 10k dei bus
1;OPA1612AIDR;SOIC-8_3.9x4.9mm_P1.27mm;U21;shaper F
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
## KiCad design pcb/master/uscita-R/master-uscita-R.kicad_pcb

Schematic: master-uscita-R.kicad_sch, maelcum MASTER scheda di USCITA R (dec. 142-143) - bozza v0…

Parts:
C1, C2: 1000u 35V; CP_Radial_D12.5mm_P5.00mm
C3, C4: 100n 50V; C_0805_2012Metric
C5, C7: 10u 35V; CP_Radial_D5.0mm_P2.00mm
C6, C8: 47u 35V; CP_Radial_D6.3mm_P2.50mm
C9, C10, C11, C12, C13, C14, C16, C17, C19, C20: 100n; C_0805_2012Metric
C15, C18: 15n C0G; C_1206_3216Metric
C21: 1u; C_1206_3216Metric
D1, D3, D5, D6, D7, D8, D9, D10, D11, D12, D13, D14, D15, D16, D17, D18, D19, D20, D21, D22, D23, D24, D25, D26, D27, D28, D29, D30, D31, D32, D33, D34, D35, D36, D37, D38, D39, D40, D43: 1N4148W; D_SOD-123
D2, D4: S1G; D_SMA
D41, D42: BAT54W; SOT-323_SC-70
FB1, FB2: ferrite 600R 2A; L_1206_3216Metric
H1, H2: CHASSIS; MountingHole_3.2mm_M3_Pad
J1: C96 maschio; DIN41612_C_3x32_Male_Horizontal_THT
J2: 2x7 cavo piatto; PinHeader_2x07_P2.54mm_Vertical
J3: 2x5 cavo; PinHeader_2x05_P2.54mm_Vertical
K1, K2: G6K-2F DC5; Relay_DPDT_Omron_G6K-2F
Q1, Q3, Q8, Q10: BF245A; TO-92_Inline_Wide
Q2, Q6, Q9, Q13: MJE340; TO-126-3_Vertical
Q4, Q7, Q11, Q14: MJE350; TO-126-3_Vertical
Q5, Q12: BC847B; SOT-23
Q15: AO3400A; SOT-23
Q16: 2N7002; SOT-23
R1, R3: 120 1%; R_0805_2012Metric
R2, R4: 1k62 1%; R_0805_2012Metric
R5, R6, R32: 10k 0.1%; R_0805_2012Metric
R7, R8, R9, R10, R20, R21: 47; R_0805_2012Metric
R11, R22: 2k2 1%; R_0805_2012Metric
R12, R23: 1k 1%; R_0805_2012Metric
R13, R14, R24, R25: 33 1%; R_1206_3216Metric
R15, R17, R26, R27, R29: 1k 0.1%; R_0805_2012Metric
R16, R18, R28: 1M 1%; R_0805_2012Metric
R19, R30: 220k 1%; R_0805_2012Metric
R31: 100k 0.1%; R_0805_2012Metric
R33, R35: 118k 1%; R_0805_2012Metric
R34, R36, R37, R38: 10k 1%; R_0805_2012Metric
R39, R41: 4k7; R_0805_2012Metric
R40: 680k; R_0805_2012Metric
R42, R46: 10k; R_0805_2012Metric
R43: 100; R_0805_2012Metric
R44: 100k; R_0805_2012Metric
R45: 1k; R_0805_2012Metric
U1, U2, U11, U21: OPA1612AIDR; SOIC-8_3.9x4.9mm_P1.27mm
U3: LM339; SOIC-14_3.9x8.7mm_P1.27mm
U12, U22: TL071; SOIC-8_3.9x4.9mm_P1.27mm
U40: LM317; TO-220-3_Vertical
U41: LM337; TO-220-3_Vertical

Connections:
+5V: D43.1 (K), J1.a21, J1.a22, K1.1, K2.1, R37.1, R40.1, R42.1, R44.2, R46.2
+18V: C6.1, C9.1, C11.1, C13.1, C16.1, C19.1, D1.1 (K), D2.2 (A), R1.1, U1.8 (V+), U2.8 (V+), U3.3 (V+), U12.7 (V+), U22.7 (V+), U40.2 (VO)
-18V: C8.2, C10.2, C12.2, C14.2, C17.2, C20.2, D3.2 (A), D4.1 (K), R3.1, U1.4 (V-), U2.4 (V-), U3.12 (V-), U12.4 (V-), U22.4 (V-), U41.3 (VO)
ADJ+: C5.1, D1.2 (A), R1.2, R2.1, U40.1 (ADJ)
ADJ-: C7.2, D3.1 (K), R3.2, R4.1, U41.1 (ADJ)
AGND: C1.2, C2.1, C3.2, C4.1, C5.2, C6.2, C7.1, C8.1, C9.2, C10.1, C11.2, C12.1, C13.2, C14.1, C16.2, C17.1, C19.2, C20.1, J1.a13, J1.a14, J1.a15, J1.a16, J1.a17, J1.a18, J1.a19, J1.a20, J2.1, J2.3, J2.5, J2.7, J2.9, J2.11, J3.1, J3.4, J3.7, J3.10, R2.2, R4.2, R18.2, R29.2, R32.2, R34.2, R36.2, U2.3 (+), U2.5 (+), U3.11 (+), U12.3 (+), U22.3 (+)
B2_C: Q12.2 (E), Q14.3 (B), R23.2
B2_H: Q5.2 (E), Q7.3 (B), R12.2
BC: R6.2, R8.1, U2.1
BH: R7.1, U1.6 (-), U1.7
BIN: R5.2, R6.1, U2.2 (-)
BOC: K2.6, R8.2
BOH: K2.3, R7.2
BOOTH_R: J2.8, R5.1, U1.5 (+)
BU_C: D23.2 (A), Q8.2 (S), Q9.3 (B), R20.2
BU_H: D5.2 (A), Q1.2 (S), Q2.3 (B), R9.2
CHALF: R37.2, R38.1, U3.9 (+)
CHASSIS: H1.1, H2.1, J1.a25, J1.a26
CLAT: C21.1, D41.3 (K), R39.2, R40.2, U3.8 (-)
CLD: R31.2, R32.1, U3.5 (+), U3.6 (-)
CLIP_R: D42.3 (K), J2.14, R41.2, R42.2
CLO: R41.1, U3.14
CLX: R39.1, U3.1, U3.2
CTN: R35.2, R36.1, U3.4 (-)
CTP: R33.2, R34.1, U3.7 (+), U3.10 (-)
CTRL_GND: C21.2, D41.1 (A), D42.1 (A), J1.a23, J1.a24, J1.c16, J1.c20, J1.c24, J1.c28, Q15.2 (S), Q16.2 (S), R38.2
DRV_C: Q12.3 (C), Q13.3 (B), R22.1, U21.1
DRV_H: Q5.3 (C), Q6.3 (B), R11.1, U11.1
E1_C: Q13.1 (E), R24.1
E1_H: Q6.1 (E), R13.1
E2_C: Q14.1 (E), R25.1
E2_H: Q7.1 (E), R14.1
GLOBAL_MUTE: J1.c9, R44.1, R45.1
GMG: Q16.1 (G), R45.2
INN_C: R26.2, R27.2, U21.2 (-)
INN_H: R17.2, R18.1, U11.2 (-)
INP_C: R28.2, R29.1, U21.3 (+)
INP_H: R15.2, R16.2, U11.3 (+)
J1S_C: Q8.1 (G), R20.1
J1S_H: Q1.1 (G), R9.1
J2S_C: Q10.1 (G), R21.1
J2S_H: Q3.1 (G), R10.1
KD: D43.2 (A), K1.8, K2.8, Q15.3 (D)
KG: Q15.1 (G), R43.2
KG0: Q16.3 (D), R43.1, R46.1
MAST_R: J2.4, U1.3 (+)
MID_C: Q12.1 (B), R22.2, R23.1
MID_H: Q5.1 (B), R11.2, R12.1
MRX: R15.1, R26.1, U1.1, U1.2 (-)
NB2_C: D40.1 (K), Q10.3 (D), Q11.3 (B)
NB2_H: D22.1 (K), Q3.3 (D), Q4.3 (B)
NU: U2.6 (-), U2.7
OUT_C: D31.1 (K), D32.2 (A), K1.6, R24.2, R25.2, R27.1, R30.1, U21.5 (+)
OUT_H: D13.1 (K), D14.2 (A), K1.3, R13.2, R14.2, R17.1, R19.1, R31.1, U11.5 (+)
RAW+26: FB1.1, J1.a9, J1.a10
RAW-26: FB2.1, J1.a11, J1.a12
S1_C: D23.1 (K), D24.2 (A)
S1_H: D5.1 (K), D6.2 (A)
S2_C: D24.1 (K), D25.2 (A)
S2_H: D6.1 (K), D7.2 (A)
S3_C: D25.1 (K), D26.2 (A)
S3_H: D7.1 (K), D8.2 (A)
S4_C: D26.1 (K), D27.2 (A)
S4_H: D8.1 (K), D9.2 (A)
S5_C: D27.1 (K), D28.2 (A)
S5_H: D9.1 (K), D10.2 (A)
S6_C: D28.1 (K), D29.2 (A)
S6_H: D10.1 (K), D11.2 (A)
S7_C: D29.1 (K), D30.2 (A)
S7_H: D11.1 (K), D12.2 (A)
S8_C: D30.1 (K), D31.2 (A)
S8_H: D12.1 (K), D13.2 (A)
SVN_C: C18.1, R30.2, U22.2 (-)
SVN_H: C15.1, R19.2, U12.2 (-)
SV_C: C18.2, R28.1, U22.6
SV_H: C15.2, R16.1, U12.6
T1_C: D32.1 (K), D33.2 (A)
T1_H: D14.1 (K), D15.2 (A)
T2_C: D33.1 (K), D34.2 (A)
T2_H: D15.1 (K), D16.2 (A)
T3_C: D34.1 (K), D35.2 (A)
T3_H: D16.1 (K), D17.2 (A)
T4_C: D35.1 (K), D36.2 (A)
T4_H: D17.1 (K), D18.2 (A)
T5_C: D36.1 (K), D37.2 (A)
T5_H: D18.1 (K), D19.2 (A)
T6_C: D37.1 (K), D38.2 (A)
T6_H: D19.1 (K), D20.2 (A)
T7_C: D38.1 (K), D39.2 (A)
T7_H: D20.1 (K), D21.2 (A)
T8_C: D39.1 (K), D40.2 (A)
T8_H: D21.1 (K), D22.2 (A)
UB_C: U21.6 (-), U21.7
UB_H: U11.6 (-), U11.7
V26F+: C1.1, C3.1, D2.1 (K), FB1.2, Q1.3 (D), Q2.2 (C), Q6.2 (C), Q8.3 (D), Q9.2 (C), Q13.2 (C), R33.1, U40.3 (VI)
V26F-: C2.2, C4.2, D4.2 (A), FB2.2, Q3.2 (S), Q4.2 (C), Q7.2 (C), Q10.2 (S), Q11.2 (C), Q14.2 (C), R10.2, R21.2, R35.1, U41.2 (VI)
VM_C: Q11.1 (E), U21.4 (V-)
VM_H: Q4.1 (E), U11.4 (V-)
VP_C: Q9.1 (E), U21.8 (V+)
VP_H: Q2.1 (E), U11.8 (V+)
XBC: J3.6, K2.5
XBH: J3.5, K2.4
XMC: J3.3, K1.5
XMH: J3.2, K1.4

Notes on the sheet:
BACKPLANE C96 (classe MASTER-OUT, dec. 143): solo alimentazioni
ALIMENTAZIONE [M]: statici +-26 filtrati, +-18 locali (LM317/337)
RICEVITORE del MASTER e DRIVER del BOOTH [B3] (OPA1612 diretto, §3.4)
STADIO D'USCITA caldo [F]+[G] (bootstrap, dec. 86)
STADIO D'USCITA freddo [F]+[G] (bootstrap, invertente)
CLIP detector: finestra sul caldo, soglia 0,86 x statico, tenuta ~0,5 s (NOTA, da simulare)
RELE' di MASTER e BOOTH (G6K-2F, 5 V, 237 ohm; eccitati = suono, failsafe)
COMANDO DEI RELE' dalla GLOBAL_MUTE (c9): basso = suona
CONNETTORI: J2 dalla scheda di segnale, J3 verso la schedina dei connettori sul retro
